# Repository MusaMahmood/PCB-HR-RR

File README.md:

# PCB-HR-RR
&lt;work in progress>

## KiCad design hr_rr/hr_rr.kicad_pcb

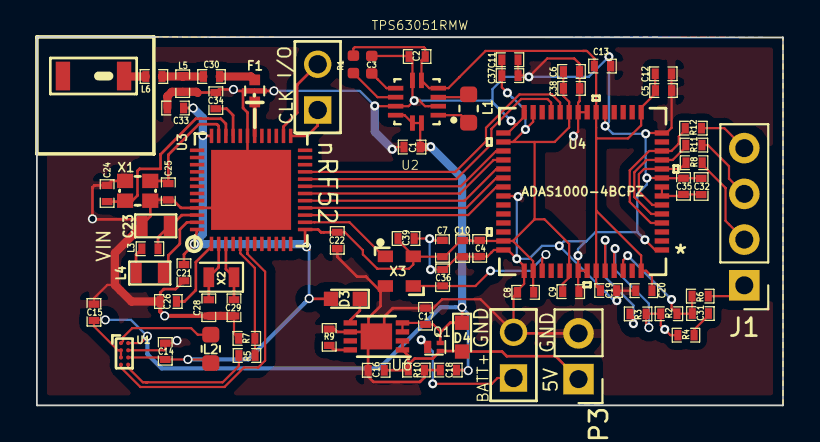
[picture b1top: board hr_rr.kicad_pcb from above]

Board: 2 copper layers, 41.5 x 20.5 mm, 73 parts (0 on the bottom side), 52 nets.

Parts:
A1: CHIP-ANT; JTI-2450AT18A100-CHIP-ANT
C1: 10µF; SM0402
C2: 22µF; SM0402
C3: 1nF; C_0402_1005Metric
C4, C5, C16, C17: 4.7uF; SM0402
C6, C7, C8, C9, C10, C11, C12, C13, C19, C20, C32, C39: 0.1uF; SM0402
C14, C15, C35: 10uF; SM0402
C18: 1.0uF; SM0402
C21: 4.7µF; SM0402
C22, C26, C33: 100nF; SM0402
C23: 1.0µF; SM0603
C24, C25, C28, C29: 12pF; SM0402
C30: 1.0pF; SM0402
C31: 2.2 nF; SM0402
C34: 100pF; SM0402
C36: 15pF; SM0402
C37, C38: 2.2uF; SM0402
D3: LED; LED_0603
D4: D_Schottky; LED_0603
F1: 2450FM07A0029; R_0402
J1: Electrodes; PinHeader_1x04_P2.54mm_Vertical
L1, L2: 2.20 µH; L_0603_1608Metric
L3: 15nH; SM0402
L4: 10uH; SM0603
L5: 2.7 nH; SM0402
L6: 3.9 nH; SM0402
P1, P2: Conn_01x02_Male; PIN_ARRAY_2X1
P3: Conn_01x02_Male; Pin_Header_Straight_1x02_Pitch2.54mm
Q1: DMP21D5UFB4-7B; X2-DFN1006
R1: 1M; R_0402_1005Metric
R2: 4M; SM0402
R3: 40k; SM0402
R4, R10: 100k; SM0402
R5, R7: 1M; SM0402
R6, R8, R11, R12: 30k; SM0402
R9: 2k; SM0402
U1: TPS62746; XBGA-8
U2: TPS63051RMW; QFN50P250X250X100-12N
U3: NRF528XX-QFAA; UQFN-48-1EP_6x6mm_Pitch0.4mm
U4: ADAS1000-4BCPZ
U6: MCP73831; DFN-8-1EP_3x2mm_Pitch0.5mm
X1: Crystal_GND24; CRYSTAL-SMD-2.0MMx1.6MM
X2: 32.768 kHz; Crystal_SMD_2012-2pin_2.0x1.2mm
X3: DSC1001; DSC1001DI5-008.1920T

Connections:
1.8V_supply: C4.2, C6.2, C7.2, C8.2, C9.2, C10.2, C11.2, C14.1, C21.2, C22.1, C33.2, C37.2, C38.2, C39.2, D3.2, L2.2, U1.C2, U3.13, U3.36, U3.48, U4.23, U4.27, U4.30, U4.41, U4.44, U4.48, X3.4
3.3V_supply: C2.1, C5.2, C12.2, C13.2, C19.2, C20.2, R1.1, U2.4, U2.5, U4.15, U4.20, U4.51, U4.56
5V_in_charge: C16.1, D4.2, P3.1, Q1.1, R10.1, U6.1, U6.2
/AIN_BAT_DIV_VOLTAGE: R5.2, R7.2, U3.5
/CLK_DSC1001_STANDBY: U3.14, X3.1
/DEC1: C26.1, U3.1
/DEC3: C34.1, U3.33
/DSC1001_CLK_OUT: C36.1, U4.45, X3.3
/LOAD_SW_CTRL: U1.D1, U3.6
/RF: C30.1, F1.4
/RLD_BIAS_ELECTRODE: J1.1, R6.2
/SCLK: U3.18, U4.32
/SDI: U3.17, U4.33
/SDO: U3.19, U4.31
/SWDCLK: P2.1, U3.25
/SWDIO: P2.2, U3.26
/VREF: C32.1, C35.1, U4.7, U4.8
/e_LA: J1.2, R8.1
/e_LL: J1.3, R11.1
/e_RA: J1.4, R12.1
/~CS: U3.15, U4.35
/~DRDY: U3.16, U4.34
/~PWDN: U3.20, U4.25
/~RESET: U3.21, U4.24
BATT_V: P1.1, Q1.2
DGND: C1.2, C2.2, C3.2, C4.1, C5.1, C6.1, C7.1, C8.1, C9.1, C10.1, C11.1, C12.1, C13.1, C14.2, C15.2, C16.2, C17.2, C18.1, C19.1, C20.1, C21.1, C22.2, C23.2, C24.1, C25.1, C26.2, C28.2, C29.2, C32.2, C33.1, C34.2, C35.2, C36.2, C37.1, C38.1, C39.1, F1.1, F1.3, L5.2, P1.2, P3.2, R7.1, R9.2, R10.2, U1.B2, U2.2, U2.6, U2.9, U3.31, U3.45, U3.49, U4.1, U4.9, U4.14, U4.19, U4.21, U4.22, U4.28, U4.29, U4.36, U4.42, U4.43, U4.49, U4.50, U6.6, U6.9, X1.2, X1.4, X3.2
unnamed: A1.1, L6.2
unnamed: C3.1, U2.7
unnamed: C23.1, L3.2, U3.46
unnamed: C24.2, U3.34, X1.1
unnamed: C25.2, U3.35, X1.3
unnamed: C28.1, U3.2, X2.2
unnamed: C29.1, U3.3, X2.1
unnamed: C30.2, L5.1, L6.1
unnamed: C31.1, R4.1
unnamed: C31.2, R2.1, R6.1, U4.54
unnamed: D3.1, U6.5
unnamed: F1.2, U3.30
unnamed: L1.1, U2.3
unnamed: L1.2, U2.1
unnamed: L2.1, U1.A1
unnamed: L3.1, L4.2
unnamed: L4.1, U3.47
unnamed: R1.2, U2.8
unnamed: R2.2, R3.2, R4.2, U4.53
unnamed: R3.1, U4.52
unnamed: R5.1, U1.D2
unnamed: R8.2, U4.6, U4.10
unnamed: R9.1, U6.8
unnamed: R11.2, U4.5, U4.11
unnamed: R12.2, U4.4, U4.12
Vcc<BATT>: C1.1, C15.1, C17.1, C18.2, D4.1, Q1.3, U1.A2, U1.B1, U1.C1, U2.10, U2.11, U2.12, U6.3, U6.4

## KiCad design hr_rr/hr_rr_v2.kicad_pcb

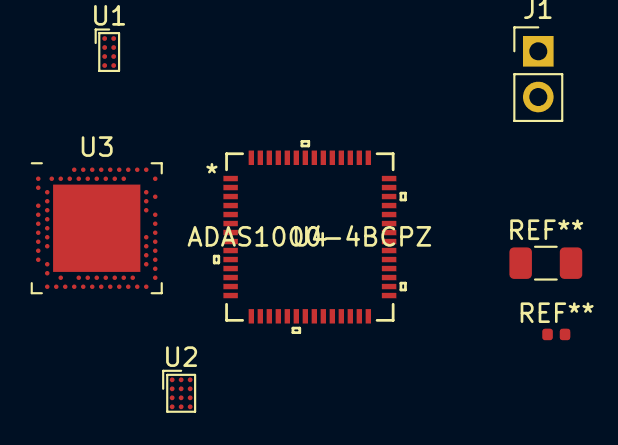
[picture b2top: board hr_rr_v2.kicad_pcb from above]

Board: 2 copper layers, 5 parts (0 on the bottom side), 2 nets, no tracks yet.

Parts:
J1: Conn_01x02_Male; PinHeader_1x02_P2.54mm_Vertical
U1: TPS62746; Texas_DSBGA-8_0.9x1.9mm_Layout2x4_P0.5mm
U2: TPS63051_YFF; Texas_DSBGA-12_1.36x1.86mm_Layout3x4_P0.5mm
U3: nRF52840; Nordic_AQFN-73-1EP_7x7mm_P0.5mm
U4: ADAS1000-4BCPZ

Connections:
unnamed: U3.A22, U3.AD14, U3.AD23, U3.B1, U3.W1
unnamed: U3.B7, U3.EP

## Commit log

2018-10-25 ADAS1000 Libraries + Starting Schematic.
2018-10-25 Added necessary components to schematic, pcb. Need to route, and add passive components.
2018-10-25 Updated Power Supply Circuitry.
2018-10-26 Restored original nRF52832 design.
2018-10-26 Restored old PCB, reassigned new one. Removed unneeded components.
2018-10-26 Updated components with new voltage regulators in schematic.
2018-10-26 Cleaned PCB of old voltage regulators.
2018-10-26 Remove old/unneeded files.
2018-10-26 Updated Component-Footprint Associations for Voltage Regulators.
2018-10-26 Minor adjustments to schematic, cleanup.
2018-10-26 Updated all outdated footprint associations. Updated PCB to include new footprints (not wired).
2018-10-26 Updated footprint to include new footprints.
2018-10-26 Changed TPS63051 to VQFN Version, integrated power components.
2018-10-28 Re-added libraries as relative paths.
2018-10-28 Added CLK sch components, updated libraries, added ADAS to schematic.
2018-10-28 Added footprint for CMOS clock, added to PCB.
2018-10-29 Completed ADAS1000-4 portion, finalized PCB.
2018-10-29 Added missing decoupling caps.
2018-10-29 Fixed via annular ring size, trace near edge.
2018-12-13 (Fixed #4) CMOS Clock Reconfigure
2018-12-13 (Fixed #3) Shorted EN, ILIM0 to Vcc, also removed PG from reset pin.
2018-12-13 Fixed #2, updated BGA pattern.

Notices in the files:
parts and their libraries:
Copyright 2016 Accelerated Designs. All rights reserved.
